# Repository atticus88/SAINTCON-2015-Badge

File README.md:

## SaintCon Badge 2015

### View the Presentation

You can view our presentation about the project on [YouTube](https://youtu.be/g20mdvsHHlY), and view the slides [here](https://docs.google.com/presentation/d/1DdALhMUuNWNRxAOWQyzCzernyqPwKxijxxV0nVtLUcg/).

### Getting Started
#### XMega-A3BU Xplained 
* For PDI programming cut jumper to disconnect JTAG from TDO from PDI DATA

#### Mac OSX
* Download CrossPack AVR Tools [CrossPack](http://www.obdev.com/downloads/crosspack/CrossPack-AVR-20131216.dmg)

#### Linux 
* Get latest version of AVRDUDE
```
$ sudo add-apt-repository ppa:pmjdebruijn/avrdude-release
$ sudo apt-get update
$ sudo apt-get install avrdude
```
* Download the latest [Atmel AVR Toolchain](http://www.atmel.com/tools/atmelavrtoolchainforlinux.aspx)
* Extract tools and add to path
```
$ tar xzf avr8-gnu-toolchain-3.4.5.1522-linux.any.x86.tar
$ export PATH=$PATH:/pathtotoolchain/avr8-gnu/bin/
```

### Contributing 
When contributing to the repository please create a new branch for the code you are working on and create a pull request when you want the code to be merged into the master branch.

```
# git checkout -b kh-esp-branch
```

### Boot-loader

The default boot-loader is now included in the project `badge-2015/xmega/bootloader/atxmega256a3bu_104.hex`

Use the following command to flash boot-loader:

```
$ avrdude -p atxmega256a3bu -P usb -c avrispmkII -U flash:w:atxmega256a3bu_104.hex
```

The xboot boot-loader is also inclueded in the project to allow for OTA updates `badge-2015/xmega/bootloader/xboot-boot.hex`
Example code doing OTA updates over Bluetooth [here](https://github.com/neonquill/nRF24L01P_xmega_lib).

Use the following command to flash the xboot boot-loader:

```
$ avrdude -p atxmega256a3bu -P usb -c avrispmkII -U boot:w:xboot-boot.hex
```

### Compile Application
```
# cd badge-2015/app/gcc
# make
# ./flash
```

### Write Application to ATXMega256A3BU
```
# avrdude -p atxmega256a3bu -P usb -c avrispmkII -U flash:w:app.hex
```

### Badge Test Application
To test the badge hardware checkout the badge-test branch. 

```
# git checkout badge-test
# cd badge-2015/app/gcc
# make
# ./flash
```

### Flashing ESP Firmware
To flash the ESP first you need to enable to USB USART Bridge. Make sure this line is un commented in `conf_usb.h`
```

#define ESP_USB_DEBUG_MODE

...
```
Make and flash the badge with the changes.

To get the badge into ESP flash mode, rotate badge into Name mode and press A. A blue light should flash on the ESP. Connect the badge to your USB and  you are ready to run esptool.py to update the firmware.

```
# python esptool.py --baud 115200 --port /dev/tty.usbmodem1451 write_flash --flash_mode dio --flash_size 32m 0x00000 nodemcu-mqtt-115200-integer-min.bin
```

Once esptool.py has finished. Restart the badge. You can verify that the ESP is running the correct version using the screen command.

```
# screen /dev/tty.usbmodem1451 115200
```  
Once connected with screen you should be able to type commands to the ESP and see the results.

### Creating BMP images
The maximum size of an images that can be compiled into the code.
(height * width) < 32768 
```
sips -s format bmp <file>.<ext> --out image.bmp
python create_image.py ili9341 image.bmp image_name > image_name.h
```

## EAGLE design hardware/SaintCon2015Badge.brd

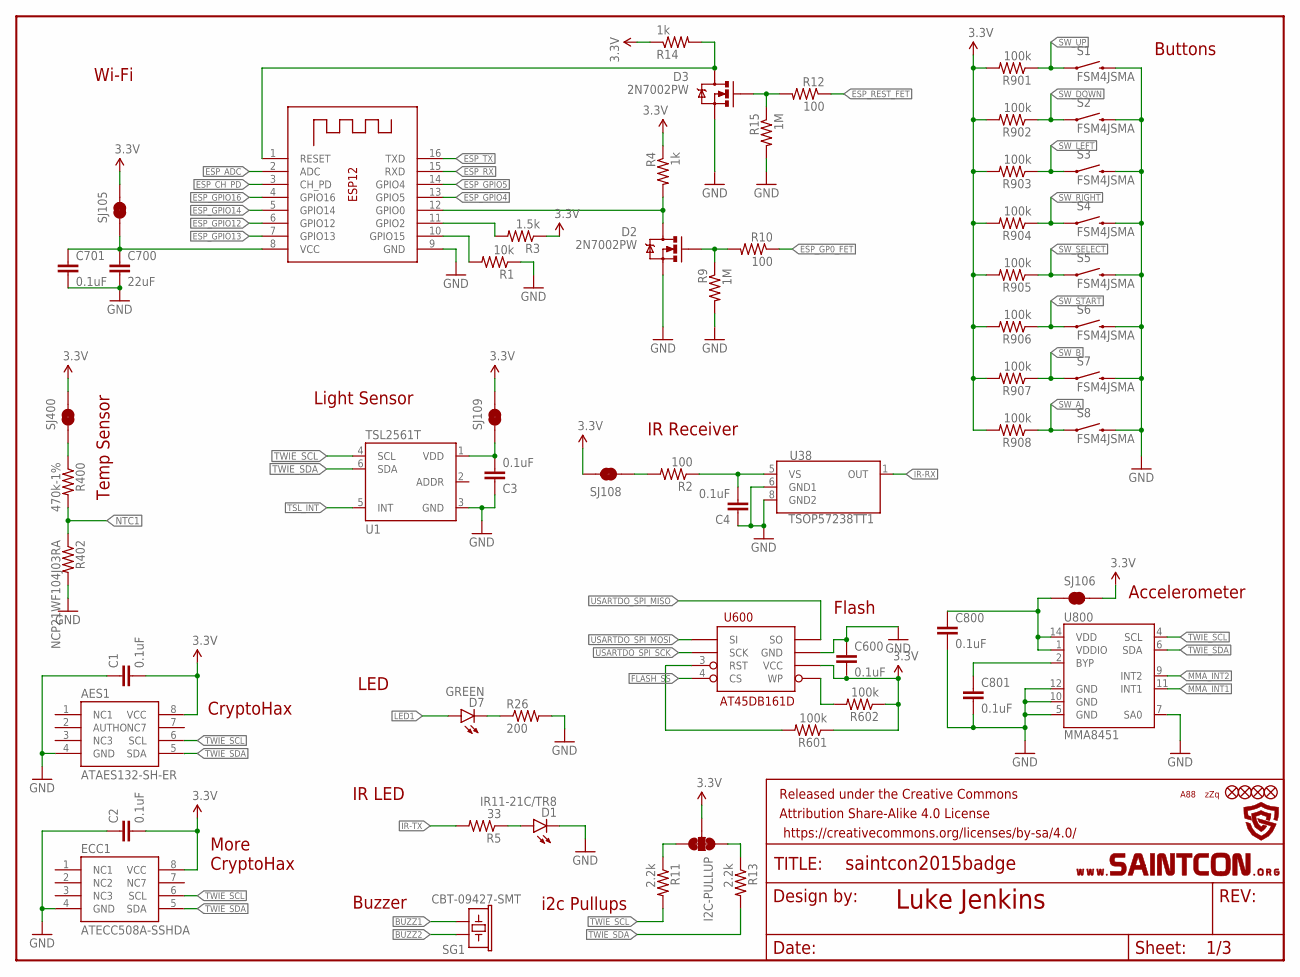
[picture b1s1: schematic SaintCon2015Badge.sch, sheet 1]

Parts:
AES1: ATAES132-SH-ER; SOIC8
C1, C2, C3, C4, C600, C701, C800, C801: 0.1uF; 0805
C700: 22uF; 0805
D1: IR11-21C/TR8; LED-1206
D2, D3: 2N7002PW; SOT323
D7: GREEN; LED-1206
ECC1: ATECC508A-SSHDA; SOIC8
ESP12: ESP12; ESP-12
FID1, FID2, FID3, FID4: FIDUCIAL1X2; FIDUCIAL-1X2
FRAME3: FRAME-LETTERNO_PACKAGE; DUMMY
I2C-PULLUP: JUMPER-PAD-3-NC_BY_TRACE; PAD-JUMPER-3-3OF3_NC_BY_TRACE_YES_SILK_FULL_BOX
R1: 10k; 0805
R2, R10, R12: 100; 0805
R3: 1.5k; 0805
R4, R14: 1k; 0805
R5: 33; 0805
R9, R15: 1M; 0805
R11, R13: 2.2k; 0805
R26: 200; 0805
R400: 470k-1%; 0805
R402: NCP21WF104J03RA; 0805
R601, R602, R901, R902, R903, R904, R905, R906, R907, R908: 100k; 0805
S1, S2, S3, S4, S5, S6, S7, S8: FSM4JSMA; TACTILE_SWITCH_ZZQ
SG1: CBT-09427-SMT; BUZZER-CCV-KIT
SJ105, SJ106, SJ108, SJ109, SJ400: JUMPER-PAD-2-NC_BY_TRACE; PAD-JUMPER-2-NC_BY_TRACE_YES_SILK
U1: TSL2561T; TMB-6
U38: TSOP57238TT1; TSOP572
U600: AT45DB161D; SO08-EIAJ
U800: MMA8451; QFN-16_0.5MM
U$1: AZZQ
U$2: A88
U$4: SAINTCON-LOGO
U$5: SAINTCON-HEADER

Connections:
3.3V: AES1.8 (VCC), C1.2, C2.2, C600.2, ECC1.8 (VCC), I2C-PULLUP.2, R3.1, R4.1, R14.1, R601.1, R602.1, R901.2, R902.2, R903.2, R904.2, R905.2, R906.2, R907.2, R908.2, SJ105.2, SJ106.2, SJ108.2, SJ109.2, SJ400.2, U600.6 (VCC); also elsewhere on the board
AT45-/RST: R601.2, U600.3 (RST)
AT45-/WP: R602.2, U600.5 (WP)
BUZZ1: SG1.+ (1); also elsewhere on the board
BUZZ2: SG1.- (2); also elsewhere on the board
D7-R26: D7.C, R26.1
ESP_ADC: ESP12.2 (ADC)
ESP_CH_PD: ESP12.3 (CH_PD); also elsewhere on the board
ESP_GP0_FET: R10.1; also elsewhere on the board
ESP_GPIO0: D2.3 (D), ESP12.12 (GPIO0), R4.2
ESP_GPIO0_FET_GATE: D2.1 (G), R9.1, R10.2
ESP_GPIO2: ESP12.11 (GPIO2), R3.2
ESP_GPIO4: ESP12.13 (GPIO5)
ESP_GPIO5: ESP12.14 (GPIO4)
ESP_GPIO12: ESP12.6 (GPIO12)
ESP_GPIO13: ESP12.7 (GPIO13)
ESP_GPIO14: ESP12.5 (GPIO14)
ESP_GPIO15: ESP12.10 (GPIO15), R1.2
ESP_GPIO16: ESP12.4 (GPIO16)
ESP_REST: D3.3 (D), ESP12.1 (RESET), R14.2
ESP_REST_FET: R12.1; also elsewhere on the board
ESP_REST_FET_GATE: D3.1 (G), R12.2, R15.1
ESP_RX: ESP12.15 (RXD); also elsewhere on the board
ESP_TX: ESP12.16 (TXD); also elsewhere on the board
ESP_VCC: C700.1, C701.1, ESP12.8 (VCC), SJ105.1
FLASH_SS: U600.4 (CS); also elsewhere on the board
GND: AES1.4 (GND), C1.1, C2.1, C3.1, C4.1, C600.1, C700.2, C701.2, C800.2, C801.2, D1.C, D2.2 (S), D3.2 (S), ECC1.4 (GND), ESP12.9 (GND), R1.1, R9.2, R15.2, R26.2, R402.2, S1.B2 (2), S2.B2 (2), S3.B2 (2), S4.B2 (2), S5.B2 (2), S6.B2 (2), S7.B2 (2), S8.B2 (2), U1.3 (GND), U38.6 (GND1), U38.8 (GND2), U600.7 (GND), U800.5 (GND), U800.7 (SA0), U800.10 (GND), U800.12 (GND); also elsewhere on the board
IR-RX: U38.1 (OUT); also elsewhere on the board
IR-RX-VS: C4.2, R2.1, U38.5 (VS)
IR-TX: R5.2; also elsewhere on the board
IR-TX-R: D1.A, R5.1
LED1: D7.A; also elsewhere on the board
MMA8451-BYP: C801.1, U800.2 (BYP)
MMA_INT1: U800.11 (INT1); also elsewhere on the board
MMA_INT2: U800.9 (INT2); also elsewhere on the board
MMA_VCC: C800.1, SJ106.1, U800.1 (VDDIO), U800.14 (VDD)
NTC1: R400.2, R402.1; also elsewhere on the board
R2-IN: R2.2, SJ108.1
R11-IN: I2C-PULLUP.3, R11.1
R13-IN: I2C-PULLUP.1, R13.1
R400-SJ400: R400.1, SJ400.1
SW_A: R908.1, S8.A2 (1); also elsewhere on the board
SW_B: R907.1, S7.A2 (1); also elsewhere on the board
SW_DOWN: R902.1, S2.A2 (1); also elsewhere on the board
SW_LEFT: R903.1, S3.A2 (1); also elsewhere on the board
SW_RIGHT: R904.1, S4.A2 (1); also elsewhere on the board
SW_SELECT: R905.1, S5.A2 (1); also elsewhere on the board
SW_START: R906.1, S6.A2 (1); also elsewhere on the board
SW_UP: R901.1, S1.A2 (1); also elsewhere on the board
TSL2561-VDD: C3.2, SJ109.1, U1.1 (VDD)
TSL_INT: U1.5 (INT)
TWIE_SCL: AES1.6 (SCL), ECC1.6 (SCL), R11.2, U1.4 (SCL), U800.4 (SCL); also elsewhere on the board
TWIE_SDA: AES1.5 (SDA), ECC1.5 (SDA), R13.2, U1.6 (SDA), U800.6 (SDA); also elsewhere on the board
USARTDO_SPI_MISO: U600.8 (SO); also elsewhere on the board
USARTDO_SPI_MOSI: U600.1 (SI); also elsewhere on the board
USARTDO_SPI_SCK: U600.2 (SCK); also elsewhere on the board

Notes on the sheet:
Luke Jenkins
Wi-Fi
Temp Sensor
CryptoHax
LED
IR LED
i2c Pullups
Buzzer
Accelerometer
Flash
Light Sensor
IR Receiver
Buttons
More CryptoHax

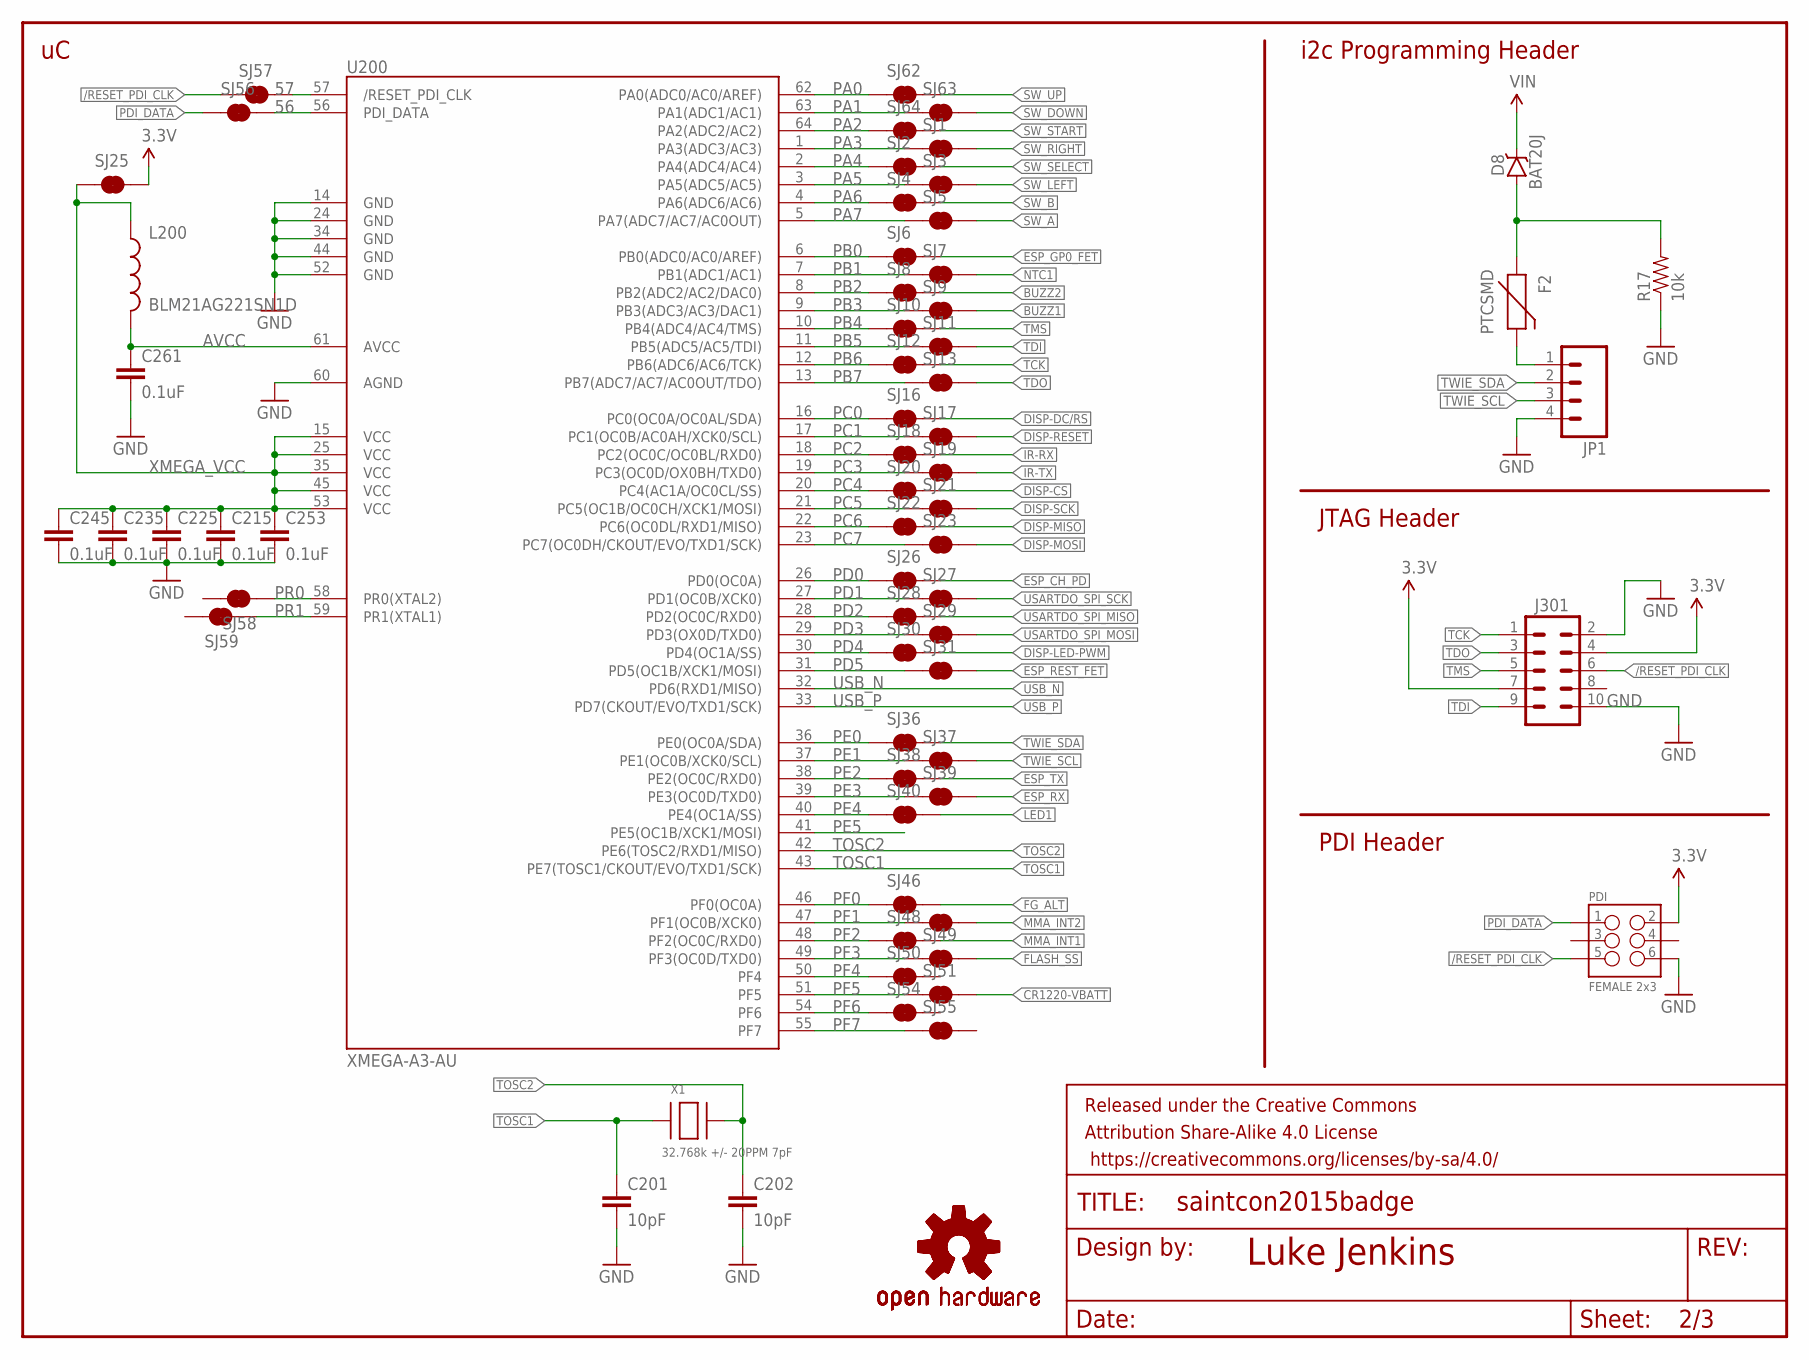
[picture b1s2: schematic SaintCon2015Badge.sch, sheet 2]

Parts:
C201, C202: 10pF; 0805
C215, C225, C235, C245, C253, C261: 0.1uF; 0805
D8: BAT20J; SOD-323
F2: PTCSMD; PTC-1206
FRAME1: FRAME-LETTERNO_PACKAGE; DUMMY
J301: M05X2PTH; AVR_ICSP
JP1: M04PTH; 1X04
L200: BLM21AG221SN1D; 0805
LOGO1: OSHW-LOGOS-COPPER; OSHW-LOGO-S_COPPER
LOGO2: OSHW-LOGOS; OSHW-LOGO-S
PDI: FEMALE 2x3; 2X3
R17: 10k; 0805
SJ1, SJ2, SJ3, SJ4, SJ5, SJ6, SJ7, SJ8, SJ9, SJ10, SJ11, SJ12, SJ13, SJ16, SJ17, SJ18, SJ19, SJ20, SJ21, SJ22, SJ23, SJ25, SJ26, SJ27, SJ28, SJ29, SJ30, SJ31, SJ36, SJ37, SJ38, SJ39, SJ40, SJ46, SJ47, SJ48, SJ49, SJ50, SJ51, SJ54, SJ55, SJ56, SJ57, SJ58, SJ59, SJ62, SJ63, SJ64: JUMPER-PAD-2-NC_BY_TRACE; PAD-JUMPER-2-NC_BY_TRACE_YES_SILK
U200: XMEGA-A3-AU; TQFP64_14X14MM
X1: 32.768k +/- 20PPM 7pF; XTAL3215

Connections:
3.3V: J301.4, J301.7, PDI.2, SJ25.2; also elsewhere on the board
56: SJ56.2, U200.56 (PDI_DATA)
57: SJ57.2, U200.57 (/RESET_PDI_CLK)
/RESET_PDI_CLK: J301.6, PDI.5, SJ57.1
AVCC: C261.1, L200.2, U200.61 (AVCC)
BUZZ1: SJ9.2; also elsewhere on the board
BUZZ2: SJ8.2; also elsewhere on the board
CR1220-VBATT: SJ51.2; also elsewhere on the board
DISP-CS: SJ20.2; also elsewhere on the board
DISP-DC/RS: SJ16.2; also elsewhere on the board
DISP-LED-PWM: SJ30.2; also elsewhere on the board
DISP-MISO: SJ22.2; also elsewhere on the board
DISP-MOSI: SJ23.2; also elsewhere on the board
DISP-RESET: SJ17.2; also elsewhere on the board
DISP-SCK: SJ21.2; also elsewhere on the board
ESP_CH_PD: SJ26.2; also elsewhere on the board
ESP_GP0_FET: SJ6.2; also elsewhere on the board
ESP_REST_FET: SJ31.2; also elsewhere on the board
ESP_RX: SJ39.2; also elsewhere on the board
ESP_TX: SJ38.2; also elsewhere on the board
F2-D8-R17: D8.A, F2.1, R17.2
FG_ALT: SJ46.2; also elsewhere on the board
FLASH_SS: SJ49.2; also elsewhere on the board
GND: C201.2, C202.2, C215.2, C225.2, C235.2, C245.2, C253.2, C261.2, J301.2, J301.10, JP1.4, PDI.6, R17.1, U200.14 (GND1), U200.24 (GND2), U200.34 (GND3), U200.44 (GND4), U200.52 (GND5), U200.60 (AGND); also elsewhere on the board
IR-RX: SJ18.2; also elsewhere on the board
IR-TX: SJ19.2; also elsewhere on the board
J1-F2: F2.2, JP1.1
LED1: SJ40.2; also elsewhere on the board
MMA_INT1: SJ48.2; also elsewhere on the board
MMA_INT2: SJ47.2; also elsewhere on the board
NTC1: SJ7.2; also elsewhere on the board
PA0: SJ62.1, U200.62 (PA0(ADC0/AC0/AREF))
PA1: SJ63.1, U200.63 (PA1(ADC1/AC1))
PA2: SJ64.1, U200.64 (PA2(ADC2/AC2))
PA3: SJ1.1, U200.1 (PA3(ADC3/AC3))
PA4: SJ2.1, U200.2 (PA4(ADC4/AC4))
PA5: SJ3.1, U200.3 (PA5(ADC5/AC5))
PA6: SJ4.1, U200.4 (PA6(ADC6/AC6))
PA7: SJ5.1, U200.5 (PA7(ADC7/AC7/AC0OUT))
PB0: SJ6.1, U200.6 (PB0(ADC0/AC0/AREF))
PB1: SJ7.1, U200.7 (PB1(ADC1/AC1))
PB2: SJ8.1, U200.8 (PB2(ADC2/AC2/DAC0))
PB3: SJ9.1, U200.9 (PB3(ADC3/AC3/DAC1))
PB4: SJ10.1, U200.10 (PB4(ADC4/AC4/TMS))
PB5: SJ11.1, U200.11 (PB5(ADC5/AC5/TDI))
PB6: SJ12.1, U200.12 (PB6(ADC6/AC6/TCK))
PB7: SJ13.1, U200.13 (PB7(ADC7/AC7/AC0OUT/TDO))
PC0: SJ16.1, U200.16 (PC0(OC0A/OC0AL/SDA))
PC1: SJ17.1, U200.17 (PC1(OC0B/AC0AH/XCK0/SCL))
PC2: SJ18.1, U200.18 (PC2(OC0C/OC0BL/RXD0))
PC3: SJ19.1, U200.19 (PC3(OC0D/OX0BH/TXD0))
PC4: SJ20.1, U200.20 (PC4(AC1A/OC0CL/SS))
PC5: SJ21.1, U200.21 (PC5(OC1B/OC0CH/XCK1/MOSI))
PC6: SJ22.1, U200.22 (PC6(OC0DL/RXD1/MISO))
PC7: SJ23.1, U200.23 (PC7(OC0DH/CKOUT/EVO/TXD1/SCK))
PD0: SJ26.1, U200.26 (PD0(OC0A))
PD1: SJ27.1, U200.27 (PD1(OC0B/XCK0))
PD2: SJ28.1, U200.28 (PD2(OC0C/RXD0))
PD3: SJ29.1, U200.29 (PD3(OX0D/TXD0))
PD4: SJ30.1, U200.30 (PD4(OC1A/SS))
PD5: SJ31.1, U200.31 (PD5(OC1B/XCK1/MOSI))
PDI_DATA: PDI.1, SJ56.1
PE0: SJ36.1, U200.36 (PE0(OC0A/SDA))
PE1: SJ37.1, U200.37 (PE1(OC0B/XCK0/SCL))
PE2: SJ38.1, U200.38 (PE2(OC0C/RXD0))
PE3: SJ39.1, U200.39 (PE3(OC0D/TXD0))
PE4: SJ40.1, U200.40 (PE4(OC1A/SS))
PE5: U200.41 (PE5(OC1B/XCK1/MOSI))
PF0: SJ46.1, U200.46 (PF0(OC0A))
PF1: SJ47.1, U200.47 (PF1(OC0B/XCK0))
PF2: SJ48.1, U200.48 (PF2(OC0C/RXD0))
PF3: SJ49.1, U200.49 (PF3(OC0D/TXD0))
PF4: SJ50.1, U200.50 (PF4)
PF5: SJ51.1, U200.51 (PF5)
PF6: SJ54.1, U200.54 (PF6)
PF7: SJ55.1, U200.55 (PF7)
PR0: SJ58.1, U200.58 (PR0(XTAL2))
PR1: SJ59.1, U200.59 (PR1(XTAL1))
SW_A: SJ5.2; also elsewhere on the board
SW_B: SJ4.2; also elsewhere on the board
SW_DOWN: SJ63.2; also elsewhere on the board
SW_LEFT: SJ3.2; also elsewhere on the board
SW_RIGHT: SJ1.2; also elsewhere on the board
SW_SELECT: SJ2.2; also elsewhere on the board
SW_START: SJ64.2; also elsewhere on the board
SW_UP: SJ62.2; also elsewhere on the board
TCK: J301.1, SJ12.2
TDI: J301.9, SJ11.2
TDO: J301.3, SJ13.2
TMS: J301.5, SJ10.2
TOSC1: C201.1, U200.43 (PE7(TOSC1/CKOUT/EVO/TXD1/SCK)), X1.P$1
TOSC2: C202.1, U200.42 (PE6(TOSC2/RXD1/MISO)), X1.P$2
TWIE_SCL: JP1.3, SJ37.2; also elsewhere on the board
TWIE_SDA: JP1.2, SJ36.2; also elsewhere on the board
USARTDO_SPI_MISO: SJ28.2; also elsewhere on the board
USARTDO_SPI_MOSI: SJ29.2; also elsewhere on the board
USARTDO_SPI_SCK: SJ27.2; also elsewhere on the board
USB_N: U200.32 (PD6(RXD1/MISO)); also elsewhere on the board
USB_P: U200.33 (PD7(CKOUT/EVO/TXD1/SCK)); also elsewhere on the board
VIN: D8.C; also elsewhere on the board
XMEGA_VCC: C215.1, C225.1, C235.1, C245.1, C253.1, L200.1, SJ25.1, U200.15 (VCC1), U200.25 (VCC2), U200.35 (VCC3), U200.45 (VCC4), U200.53 (VCC5)

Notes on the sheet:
Luke Jenkins
i2c Programming Header
JTAG Header
PDI Header

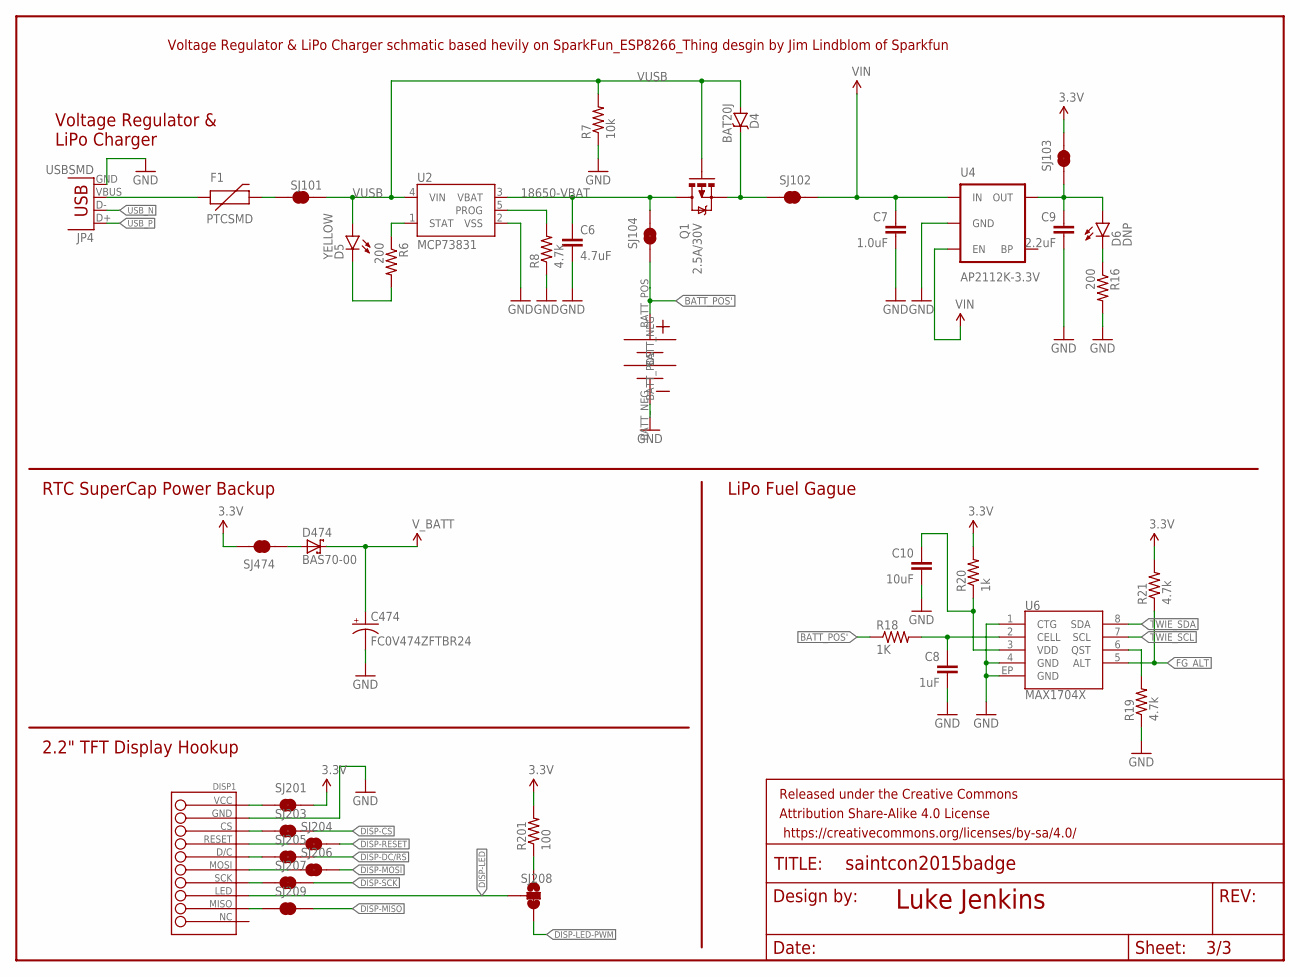
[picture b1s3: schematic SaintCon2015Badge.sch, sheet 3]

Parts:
BATT2: 1042P
C6: 4.7uF; 0805
C7: 1.0uF; 0805
C8: 1uF; 0805
C9: 2.2uF; 0805
C10: 10uF; 0805
C474: FC0V474ZFTBR24; 153CLV-1014
D4: BAT20J; SOD-323
D5: YELLOW; LED-1206
D6: DNP; LED-1206
D474: BAS70-00; SOT23
DISP1: TFT22FEMALE_SMD; TFT22
F1: PTCSMD; PTC-1206
FRAME2: FRAME-LETTERNO_PACKAGE; DUMMY
JP4: USBSMD; USB-MINIB
Q1: 2.5A/30V; SOT23-3
R6, R16: 200; 0805
R7: 10k; 0805
R8, R19, R21: 4.7k; 0805
R18: 1K; 0805
R20: 1k; 0805
R201: 100; 0805
SJ101, SJ102, SJ103, SJ104, SJ201, SJ203, SJ204, SJ205, SJ206, SJ207, SJ209, SJ474: JUMPER-PAD-2-NC_BY_TRACE; PAD-JUMPER-2-NC_BY_TRACE_YES_SILK
SJ208: JUMPER-PAD-3-2OF3_NC_BY_TRACE_SMALL; PAD-JUMPER-3-2OF3_NC_BY_TRACE_YES_SILK_FULL_BOX
U2: MCP73831; SOT23-5
U4: AP2112K-3.3V; SOT23-5
U6: MAX1704X; TDFN-8

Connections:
3.3V: R20.2, R21.2, R201.2, SJ103.2, SJ201.2, SJ474.2; also elsewhere on the board
18650-VBAT: C6.1, Q1.3 (D), SJ104.2, U2.3 (VBAT)
BATT_POS': BATT2.BATT_POS, R18.1, SJ104.1
CR1220-VBATT: C474.+, D474.3 (C); also elsewhere on the board
D4-OUT: D4.C, Q1.2 (S), SJ102.1
D5-R6: D5.C, R6.2
D6-R16: D6.C, R16.1
DISP1-CS: DISP1.CS (3), SJ203.1
DISP1-D/C: DISP1.D/C (5), SJ205.1
DISP1-MISO: DISP1.MISO (9), SJ209.1
DISP1-MOSI: DISP1.MOSI (6), SJ206.1
DISP1-RESET: DISP1.RESET (4), SJ204.1
DISP1-SCK: DISP1.SCK (7), SJ207.1
DISP1-VCC: DISP1.VCC, SJ201.1
DISP-CS: SJ203.2; also elsewhere on the board
DISP-DC/RS: SJ205.2; also elsewhere on the board
DISP-LED: DISP1.LED (8), SJ208.2
DISP-LED-100: R201.1, SJ208.1
DISP-LED-PWM: SJ208.3; also elsewhere on the board
DISP-MISO: SJ209.2; also elsewhere on the board
DISP-MOSI: SJ206.2; also elsewhere on the board
DISP-RESET: SJ204.2; also elsewhere on the board
DISP-SCK: SJ207.2; also elsewhere on the board
F1-SJ: F1.2, SJ101.1
FG_ALT: R21.1, U6.5 (ALT); also elsewhere on the board
FG_CELL: C8.1, R18.2, U6.2 (CELL)
FG_QST: R19.2, U6.6 (QST)
FG_VDD: C10.1, R20.1, U6.3 (VDD)
GND: BATT2.BATT_NEG, C6.2, C7.2, C8.2, C9.2, C10.2, C474.-, DISP1.GND (2), JP4.GND, R7.1, R8.1, R16.2, R19.1, U2.2 (VSS), U4.2 (GND), U6.1 (CTG), U6.4 (GND), U6.EP (GND); also elsewhere on the board
MCP73831-PROG: R8.2, U2.5 (PROG)
MCP73831-STAT: R6.1, U2.1 (STAT)
REG_OUT: C9.1, D6.A, SJ103.1, U4.5 (OUT)
SJ474-D474: D474.1 (A), SJ474.1
TWIE_SCL: U6.7 (SCL); also elsewhere on the board
TWIE_SDA: U6.8 (SDA); also elsewhere on the board
USB-F1: F1.1, JP4.VBUS
USB_N: JP4.D-; also elsewhere on the board
USB_P: JP4.D+; also elsewhere on the board
VIN: C7.1, SJ102.2, U4.1 (IN), U4.3 (EN); also elsewhere on the board
VUSB: D4.A, D5.A, Q1.1 (G), R7.2, SJ101.2, U2.4 (VIN)

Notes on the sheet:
Voltage Regulator & LiPo Charger
Luke Jenkins
Voltage Regulator & LiPo Charger schmatic based hevily on SparkFun_ESP8266_Thing desgin by Jim Lindblom of Sparkfun
RTC SuperCap Power Backup
2.2" TFT Display Hookup
LiPo Fuel Gague

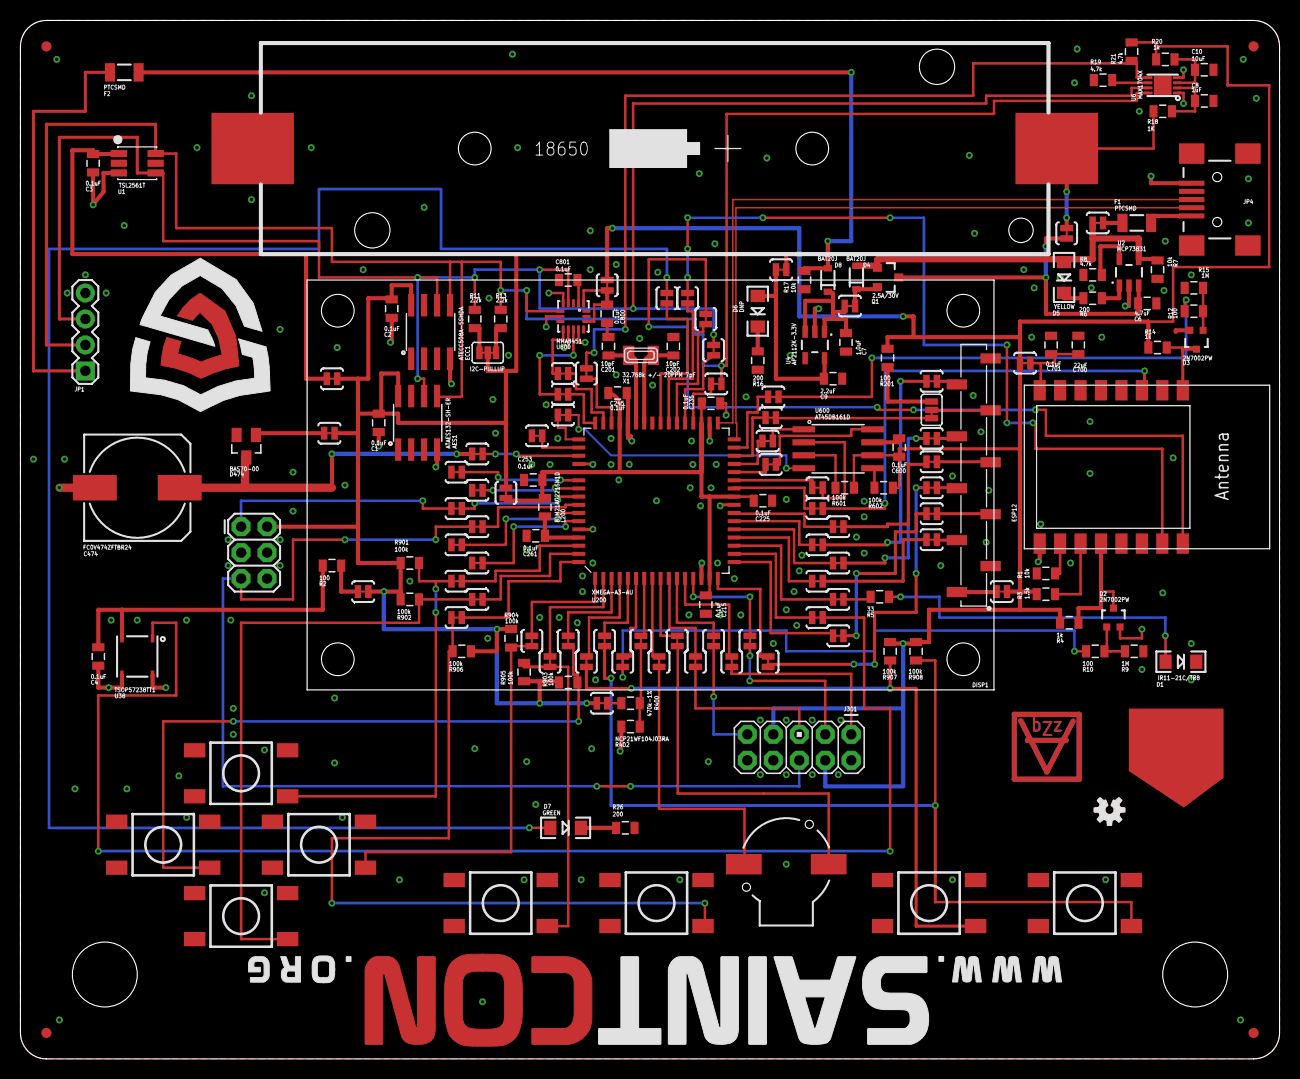
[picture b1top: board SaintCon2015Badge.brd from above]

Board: 2 copper layers, 123.2 x 101.6 mm, 178 parts (0 on the bottom side), 143 nets.

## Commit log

2015-10-30 Inital commit
2015-10-31 Initial add of hardware files
    These were the versions of the hardware files that we used to go to
    production.
2015-10-31 Add links to preso
    I think we should have a link to the presentation in the readme.
2015-11-25 changed code to not require registration change lines 497-500 to change name displayed
2016-03-23 added simple version of the mse/cmx proxy that allows clients to get their own locations without authentication

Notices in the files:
parts and their libraries:
SparkFun-Passives: Licensing: Creative Commons ShareAlike 4.0 International - https://creativecommons.org/licenses/by-sa/4.0
SparkFun-Aesthetics: Released under the Creative Commons Attribution Share-Alike 4.0 License
SparkFun-Aesthetics: https://creativecommons.org/licenses/by-sa/4.0
